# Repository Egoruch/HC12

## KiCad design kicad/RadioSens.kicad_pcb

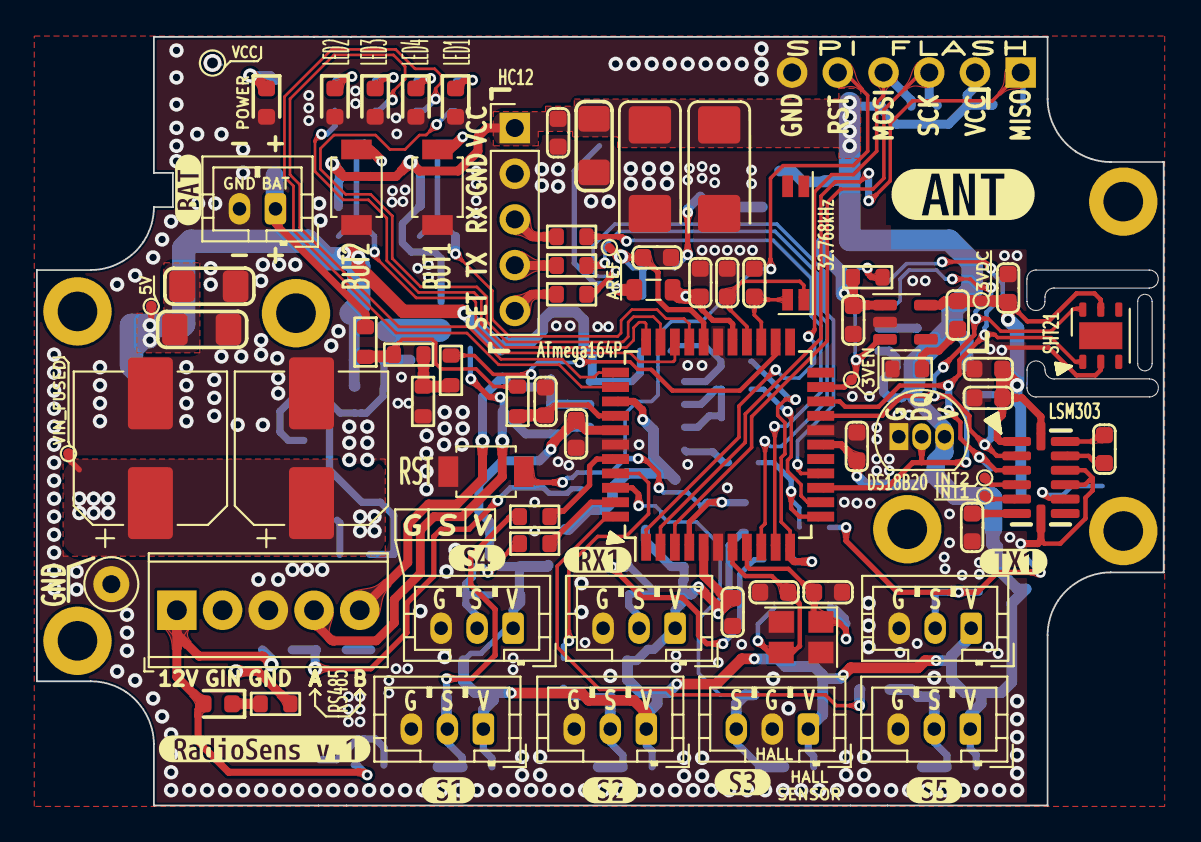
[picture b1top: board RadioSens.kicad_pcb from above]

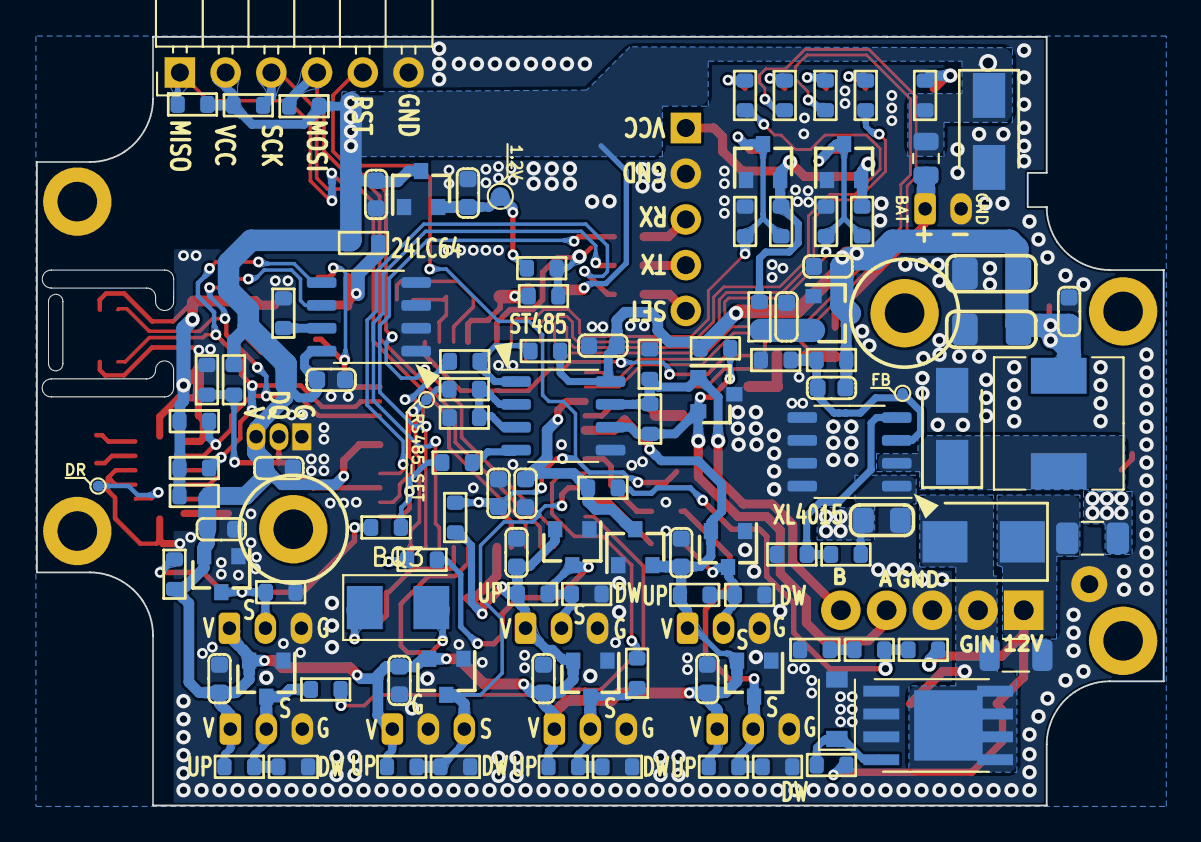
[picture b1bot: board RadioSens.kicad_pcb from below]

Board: 2 copper layers, 62.6 x 42.7 mm, 200 parts (110 on the bottom side), 81 nets.

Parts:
BQ1: KX–327L; Crystal_SMD_SeikoEpson_MC146-4Pin_6.7x1.5mm
BQ2: 3225 8MHz; Crystal_SMD_3225-4Pin_3.2x2.5mm
BQ3: 5032 8MHz; Crystal_SMD_5032-2Pin_5.0x3.2mm
C1, C7, C9, C30, C43, C45: 1u/25V; C_0603_1608Metric
C2, C6, C8, C10, C11, C12, C13, C15, C19, C22, C23, C24, C25, C36, C37, C40, C44: 0.1u/50V; C_0603_1608Metric
C3, C4: 100u/10V; CP_EIA-6032-28_Kemet-C
C5: 10u/16V; C_1206_3216Metric_Pad1.42x1.75mm_HandSolder
C14, C17: 7/50V; C_0603_1608Metric
C16, C18, C35, C41, C42: 10u/6.3V; C_0603_1608Metric
C20, C21: 22/50V; C_0603_1608Metric
C26, C27: 47u/50V; CP_Elec_8x6.5
C28: 1u/50V; C_0805_2012Metric_Pad1.15x1.40mm_HandSolder
C29: 3.3n/50V; C_0603_1608Metric
C31, C32, C33, C34: 100u/6.3V; C_1206_3216Metric_Pad1.42x1.75mm_HandSolder
C38: 4.7u/6.3V; C_0603_1608Metric
C39: 0.22u/50V; C_0603_1608Metric
C46: 2.2u/25V; C_0603_1608Metric
DA1: HC-12; HC12_PLS
DA2: XC6206P122MR-G; SOT-23
DA3: XL1509; SOP-8_3.9x4.9mm_P1.27mm
DA4: SHT21; DFN-6-1EP_3x3mm_P1mm_EP1.5x2.4mm
DA5: XC6206P332MR; SOT-23
DA6: LP2981-30DBVR; SOT-23-5
DD1: ATmega164PV-10AU; TQFP-44_10x10mm_P0.8mm
DD2: ST485; SOP-8_3.9x4.9mm_P1.27mm
DD3: DS18B20; TO-92_Inline
DD4: LSM303DLHC; LGA-14_3x5mm_P0.8mm_HandSoldering
DD5: 24LC64; SOP-8_3.9x4.9mm_P1.27mm
FU1: 0.3A; Fuse_0805_2012Metric
FU2: 1A; Fuse_1206_3216Metric
HL1, HL2, HL3, HL4, HL5, HL6: RED; LED_0603_1608Metric
J1, J2, J3, J4, J5, J6: Spacer M2; MountingHole_2.2mm_M2_DIN965_Pad
L1: 10u; L_0805_2012Metric
L2: 47uH/2A; L_Wuerth_HCM-7050
R1, R2, R3, R29, R30, R49, R50, R61, R66, R71: 0; R_0603_1608Metric
R4, R5, R6, R16, R17, R18: 22; R_0603_1608Metric
R7, R8, R9, R11, R68: 10k; R_0603_1608Metric
R10: 120; R_0603_1608Metric
R12, R19, R20, R21, R27, R47, R48, R51, R52, R53, R54, R59, R60, R62, R64, R69, R70: 4.7k; R_0603_1608Metric
R13, R14, R22, R23, R24, R25, R31, R33, R34, R36, R37, R38, R39, R41, R42, R44, R45, R67: 300k; R_0603_1608Metric
R15, R26, R28, R35, R40, R43, R46, R65: 100; R_0603_1608Metric
R32, R55, R56: 100k; R_0603_1608Metric
R57: 3.1k; R_0603_1608Metric
R58: 1k; R_0603_1608Metric
R63: 0; R_1206_3216Metric
R72: 1; R_0603_1608Metric
SB1, SB2, SB3: 3x4mm; SW_SPST_B3U-1000P
VD1: CDSOT23-SM712; SOT-23
VD2, VD3, VD4, VD6, VD7, VD8, VD9, VD10, VD14, VD15: BAT54S.215; SOT-23
VD5: SMAJ5.0A; D_SMA
VD11: MBRA340T3G; D_SMA
VD12: SMBJ28CA; D_SMB
VD13: BZT52-C9V1; D_SOD-123
VT1: SIR182DP; PowerPAK_SO-8_Single_HandSoldering
XB1, XB5, XB6, XB7, XB8, XB9, XB10, XB11, XB12: XB_TP_0.6MM; TestPoint_Pad_D0.6mm
XB2, XB3: XB_TP_1.0MM; TestPoint_Pad_D1.0mm
XB4: XB_TP_0.5MM; TestPoint_Pad_D0.5mm
XP9: Testpoint; TestPoint_Loop_D2.50mm_Drill1.0mm_LowProfile
XT1: DG308-2.54-05P-14-00A[H]; TerminalBlock_DG308-2.54-05P-14-00A(H)
XT2, XT3, XT5, XT6, XT7, XT8, XT10: NXW-03; JST_PH_B3B-PH-K_1x03_P2.00mm_Vertical
XT4: NXW-02; JST_PH_B2B-PH-K_1x02_P2.00mm_Vertical
XT9: PLS2.54-6; PinHeader_1x06_P2.54mm_Horizontal
kibuzzard-633978AE: G***; kibuzzard-633978AE
kibuzzard-633978C2: G***; kibuzzard-633978C2
kibuzzard-633978F6: G***; kibuzzard-633978F6
kibuzzard-633979A2: G***; kibuzzard-633979A2
kibuzzard-6339783C: G***; kibuzzard-6339783C
kibuzzard-6339785C: G***; kibuzzard-6339785C
kibuzzard-6339789C: G***; kibuzzard-6339789C
kibuzzard-63397779: G***; kibuzzard-63397779
kibuzzard-63397848: G***; kibuzzard-63397848
kibuzzard-63397852: G***; kibuzzard-63397852

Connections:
3V_EN: DA6.3 (ON/OFF), DD1.21 (PC2_PCINT18/TCK), R71.1, XB11.1
5V: C1.1, C29.1, C30.1, C31.1, C32.1, C33.1, C34.1, C41.1, DA5.3 (IN), DD2.8 (VCC), L2.2, R8.2, R9.2, R57.1, XB7.1
12V: FU2.1, HL6.2 (C), R62.1, R67.1, VD12.1 (C), XT1.1
/3VDC: C35.1, C36.1, C37.1, C46.2, DA4.5 (VDD), DA6.5 (VOUT), DD4.1 (VDDIO), DD4.14 (VDD), R3.2, R59.1, R60.1, XB12.1
/Battery/BAT_UNFUSED: FU1.2, R31.1, XT4.1
/DC-DC XL1509/EN: DA3.4 (EN), R55.2, R56.1
/DC-DC XL1509/FB: C29.2, DA3.3 (FB), R57.2, R58.1, XB6.1
/DC-DC XL1509/OUT: DA3.2 (OUT), L2.1, VD11.1 (C)
/DC-DC XL1509/VIN_FUSED: C26.1 (+), C27.1 (+), C28.1, DA3.1 (VIN), FU2.2, R55.1, XB5.1
/GND_RAW: R63.2, R64.1, VD12.2 (A), VT1.5 (D), VT1.6 (D), VT1.7 (D), VT1.8 (D), XT1.2
/IIC Connector/C1: C38.1, DD4.6 (C1)
/IIC Connector/INT1: DD4.5 (INT1), XB9.1
/IIC Connector/INT2: DD4.4 (INT2), XB8.1
/IIC Connector/SETC: C39.1, DD4.13 (SETC)
/IIC Connector/SETP: C39.2, DD4.12 (SETP)
/RS485/A_RS485: DD2.6 (A), R9.1, R10.2, VD1.2 (C2), XT1.4
/RS485/B_RS485: DD2.7 (B), R10.1, R11.2, VD1.1 (C1), XT1.5
/RS485/DE: DD2.2 (RE), DD2.3 (DE), R5.2, R7.2
/Sensor 1/SIGNAL: R13.2, R14.1, R15.2, VD2.3 (CA), XT2.2
/Sensor 2/SIGNAL: R38.2, R39.1, R40.2, VD8.3 (CA), XT6.2
/Sensor 4/SIGNAL: R41.2, R42.1, R43.2, VD9.3 (CA), XT7.2
/Sensor 5/SIGNAL: R44.2, R45.1, R46.2, VD10.3 (CA), XT8.2
/Sensor 6/SIGNAL: R24.2, R25.1, R26.2, VD4.3 (CA), XT3.2
/Sensor 7/SIGNAL: R33.2, R34.1, R35.2, VD6.3 (CA), XT5.2
/Voltage Regulator 3.3V/VOUT: C42.1, DA5.2 (OUT), R1.2
/Voltage Regulator 3V/VIN: C45.1, DA6.1 (VIN), R2.2, R71.2
ADC_BAT_VOL: C9.1, DD1.37 (PA0_ADC0/PCINT0), R28.1
ADC_EXTERN_VOL: C43.1, DD1.36 (PA1_ADC1/PCINT1), R65.1, VD14.3 (CA)
AREF: C19.2, DD1.29 (AREF), R49.2, R50.2, XB4.1
AVCC: C15.2, DD1.27 (AVCC), L1.2, R49.1
BAT_DIV_EN: DD1.24 (PC5_TDI/PCINT21), R29.1
BUT_1: DD1.30 (PA7_ADC7/PCINT7), R36.2, R37.1, SB2.1, VD7.3 (CA)
BUT_2: DD1.31 (PA6_ADC6/PCINT6), R22.2, R23.1, SB1.1, VD3.3 (CA)
DS18B20_DQ: DD1.14 (PD5_PCINT29/OC1A), DD3.2 (DQ), R19.2, R20.1
GND: BQ2.2 (GND), BQ2.4 (GND), C1.2, C2.2, C3.2 (-), C4.2 (-), C5.2, C6.2, C7.2, C8.2, C9.2, C10.2, C11.2, C12.2, C13.2, C14.2, C15.1, C16.2, C17.2, C18.2, C19.1, C20.2, C21.2, C22.2, C23.2, C24.1, C25.2, C26.2 (-), C27.2 (-), C28.2, C30.2, C31.2, C32.2, C33.2, C34.2, C35.2, C36.2, C37.2, C38.2, C40.2, C41.2, C42.2, C43.2, C44.2, C45.2, DA1.2 (GND), DA2.1 (GND), DA3.5 (GND), DA3.6 (GND), DA3.7 (GND), DA3.8 (GND), DA4.2 (VSS), DA5.1 (GND), DA6.2 (GND), DD1.6 (GND), DD1.18 (GND), DD1.28 (GND), DD1.39 (GND), DD2.5 (GND), DD3.1 (GND), DD4.7 (GND), DD4.10 (GND), DD4.11 (GND), DD5.1 (A0), DD5.2 (A1), DD5.3 (A2), DD5.4 (VSS), HL1.2 (C), HL2.2 (C), HL3.2 (C), HL4.2 (C), HL5.2 (C), R7.1, R11.1, R14.2, R20.2, R23.2, R25.2, R30.1, R34.2, R37.2, R39.2, R42.2, R45.2, R56.2, R58.2, R61.2, R63.1, R66.1, R70.2, R72.1, SB1.2, SB2.2, SB3.1, VD1.3 (DC), VD2.1 (A), VD3.1 (A), VD4.1 (A), VD5.2 (A), VD6.1 (A), VD7.1 (A), VD8.1 (A), VD9.1 (A), VD10.1 (A), VD11.2 (A), VD13.2 (A), VD14.1 (A), VD15.1 (A), VT1.1 (S), VT1.2 (S), VT1.3 (S), XP9.1, XT1.3, XT2.3, XT3.3, XT4.2, XT5.3, XT6.3, XT7.3, XT8.3, XT9.6, XT10.2
HC12_SET: DD1.15 (PD6_PCINT30/OC2B/ICP), R18.2
IIC_SCL: DA4.6 (SCL), DD1.19 (PC0_PCINT16/SCL), DD4.2 (SCL), DD5.6 (SCL), R60.2
IIC_SDA: DA4.1 (SDA), DD1.20 (PC1_PCINT17/SDA), DD4.3 (SDA), DD5.5 (SDA), R59.2
LED_1: DD1.32 (PA5_ADC5/PCINT5), R21.1
LED_2: DD1.33 (PA4_ADC4/PCINT4), R12.1
LED_3: DD1.34 (PA3_ADC3/PCINT3), R47.1
LED_4: DD1.35 (PA2_ADC2/PCINT2), R48.1
MISO: DD1.2 (PB6_PCINT14/OC3A/MISO), R53.2, XT9.1
MOSI: DD1.1 (PB5_PCINT13/ICP3/MOSI), R51.2, XT9.4
unnamed: C18.1, DA2.2 (OUT), R50.1, XB3.1
unnamed: C46.1, R72.2
unnamed: DA1.3 (RXD), R16.1
unnamed: DA1.4 (TXD), R17.1
unnamed: DA1.5 (SET), R18.1
unnamed: DD2.1 (RO), R4.2, R8.1
unnamed: DD2.4 (DI), R6.2
unnamed: DD4.9 (DRDY), XB10.1
unnamed: DD5.7 (WP), R61.1
unnamed: HL1.1 (A), R12.2
unnamed: HL2.1 (A), R21.2
unnamed: HL3.1 (A), R27.2
unnamed: HL4.1 (A), R47.2
unnamed: HL5.1 (A), R48.2
unnamed: HL6.1 (A), R64.2
unnamed: R28.2, R31.2, R32.1
unnamed: R29.2, R30.2, R32.2
unnamed: R62.2, VD13.1 (C), VT1.4 (G)
unnamed: R65.2, R67.2, R68.1
unnamed: R66.2, R68.2
RESET: C25.1, DD1.4 (~RESET), R54.2, SB3.2, XT9.5
RS485_SET: DD1.13 (PD4_PCINT28/XCK1/OC1B), R5.1, XB1.1
RXD0: DD1.9 (PD0_PCINT24/RXD0/T3*), R17.2
RXD1: DD1.11 (PD2_PCINT26/RXD1/INT0), R4.1, R26.1
SCK: DD1.3 (PB7_PCINT15/OC3B/SCK), R52.2, XT9.3
SENS_1: DD1.40 (PB0_XCK0/T0/PCINT8), R15.1
SENS_2: DD1.41 (PB1_T1/CLKO/PCINT9), R40.1
SENS_3: DD1.42 (PB2_AIN0/INT2/PCINT10), R69.2, R70.1, VD15.3 (CA), XT10.3
SENS_4: DD1.43 (PB3_AIN1/OC0A/PCINT11), R43.1
SENS_5: DD1.44 (PB4_SS/OC0B/PCINT12), R46.1
TOSC1: BQ1.4, C14.1, DD1.25 (PC6_TOSC1/PCINT22)
TOSC2: BQ1.1, C17.1, DD1.26 (PC7_TOSC2/PCINT23)
TXD0: DD1.10 (PD1_PCINT25/TXD0), R16.2
TXD1: DD1.12 (PD3_PCINT27/TXD1/INT1), R6.1, R35.1
VCC: C2.1, C3.1 (+), C4.1 (+), C5.1, C6.1, C7.1, C8.1, C10.1, C11.1, C12.1, C13.1, C16.1, C22.1, C23.1, C24.2, C40.1, C44.1, DA1.1 (VCC), DA2.3 (IN), DD1.5 (VCC), DD1.17 (VCC), DD1.38 (VCC), DD3.3 (VDD), DD5.8 (VCC), FU1.1, L1.1, R1.1, R2.1, R3.1, R13.1, R19.1, R22.1, R24.1, R27.1, R33.1, R36.1, R38.1, R41.1, R44.1, R51.1, R52.1, R53.1, R54.1, R69.1, VD2.2 (C), VD3.2 (C), VD4.2 (C), VD5.1 (C), VD6.2 (C), VD7.2 (C), VD8.2 (C), VD9.2 (C), VD10.2 (C), VD14.2 (C), VD15.2 (C), XB2.1, XT2.1, XT3.1, XT5.1, XT6.1, XT7.1, XT8.1, XT9.2, XT10.1
XTAL1: BQ2.1 (IN), BQ3.1, C20.1, DD1.8 (XTAL1)
XTAL2: BQ2.3 (OUT), BQ3.2, C21.1, DD1.7 (XTAL2)

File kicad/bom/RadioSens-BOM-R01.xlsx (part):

Project: | RadioSens v.1 | COMPANY NAME
Author:
Date: | 44722.0
Item | Qty | Reference(s) | Value | Footprint/Package | Tolerance | Type | Comment | Cost, UAH | Total cost, UAH | Buy | Link
1.0 | 1.0 | BQ1 | KX–327L | Crystal:Crystal_SMD_SeikoEpson_MC146-4Pin_6.7x1.5mm |  |  |  | 10.0 | 10 | 0 | https://www.rcscomponents.kiev.ua/product/kx-327lt-32-7680-k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
2.0 | 1.0 | BQ2 | 3225 8MHz | Crystal:Crystal_SMD_3225-4Pin_3.2x2.5mm |  |  | 4MHz optional | 21.5 | 21.5 | 0 | https://voron.ua/uk/catalog/037612
3.0 | 1.0 | BQ3 | 5032 8MHz | Crystal:Crystal_SMD_5032-2Pin_5.0x3.2mm |  |  | Extra package | 0.0 | 0 | 1 | DNP
4.0 | 5.0 | C1, C7, C9, C43, C45 | 1u/25V | Capacitor_SMD:C_0603_1608Metric | ±10% | X5R/X7R |  | 0.9 | 4.5 | 0 | https://www.rcscomponents.kiev.ua/product/1uf-25v-x7r-10-060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
5.0 | 8.0 | C2, C6, C8, C10, C11, C12, C13, C44 | 0.1u/50V | Capacitor_SMD:C_0603_1608Metric | ±10% | X5R/X7R |  | 0.9 | 7.2 | 0 | https://www.rcscomponents.kiev.ua/product/100nf-50v-x7r-10-0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
6.0 | 2.0 | C3, C4 | 100u/10V | Capacitor_Tantalum_SMD:CP_EIA-6032-28_Kemet-C |  |  | Alt: Type-B | 0.9 | 1.8 | 0 | https://www.rcscomponents.kiev.ua/product/100uf-6-3v-size-b-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
7.0 | 1.0 | C5 | 10u/16V | Capacitor_SMD:C_1206_3216Metric_Pad1.42x1.75mm_HandSolder | ±10% | X5R/X7R | Alt: 47u/50V | 4.0 | 4 | 0 | https://www.rcscomponents.kiev.ua/product/47uf-50v-ezv-smd-s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
8.0 | 1.0 | C14 | 7/50V | Capacitor_SMD:C_0603_1608Metric | ±10% | X5R/X7R | Alt: 6.8pF | 0.5 | 0.5 | 0 | https://www.rcscomponents.kiev.ua/product/6-8pf-50v-np0-0-5p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
9.0 | 2.0 | C15, C40 | 0.1u/50V | Capacitor_SMD:C_0603_1608Metric | ±10% | X5R/X7R |  | 0.9 | 1.8 | 0 | https://www.rcscomponents.kiev.ua/product/100nf-50v-x7r-10-0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
10.0 | 2.0 | C16, C35 | 10u/6.3V | Capacitor_SMD:C_0603_1608Metric | ±10% | X5R/X7R |  | 1.0 | 2 | 0 | https://www.rcscomponents.kiev.ua/product/10uf-6-3v-x5r-20-0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
11.0 | 1.0 | C17 | 7/50V | Capacitor_SMD:C_0603_1608Metric | ±10% | X5R/X7R | Alt: 6.8pF | 0.5 | 0.5 | 0 | https://www.rcscomponents.kiev.ua/product/6-8pf-50v-np0-0-5p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
12.0 | 1.0 | C18 | 10u/6.3V | Capacitor_SMD:C_0603_1608Metric | ±10% | X5R/X7R |  | 1.0 | 1 | 0 | https://www.rcscomponents.kiev.ua/product/10uf-6-3v-x5r-20-0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
13.0 | 1.0 | C19 | 0.1u/50V | Capacitor_SMD:C_0603_1608Metric | ±10% | X5R/X7R |  | 0.9 | 0.9 | 0 | https://www.rcscomponents.kiev.ua/product/100nf-50v-x7r-10-0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
14.0 | 1.0 | C20 | 22/50V | Capacitor_SMD:C_0603_1608Metric | ±10% | X5R/X7R |  | 0.4 | 0.4 | 0 | https://www.rcscomponents.kiev.ua/product/22pf-50v-np0-5-060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
15.0 | 1.0 | C21 | 22/50V | Capacitor_SMD:C_0603_1608Metric | ±10% | X5R/X7R |  | 0.4 | 0.4 | 0 | https://www.rcscomponents.kiev.ua/product/22pf-50v-np0-5-060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
16.0 | 1.0 | C22 | 0.1u/50V | Capacitor_SMD:C_0603_1608Metric | ±10% | X5R/X7R |  | 0.9 | 0.9 | 0 | https://www.rcscomponents.kiev.ua/product/100nf-50v-x7r-10-0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
17.0 | 1.0 | C23 | 0.1u/50V | Capacitor_SMD:C_0603_1608Metric | ±10% | X5R/X7R |  | 0.9 | 0.9 | 0 | https://www.rcscomponents.kiev.ua/product/100nf-50v-x7r-10-0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
18.0 | 1.0 | C24 | 0.1u/50V | Capacitor_SMD:C_0603_1608Metric | ±10% | X5R/X7R |  | 0.9 | 0.9 | 0 | https://www.rcscomponents.kiev.ua/product/100nf-50v-x7r-10-0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
19.0 | 1.0 | C25 | 0.1u/50V | Capacitor_SMD:C_0603_1608Metric | ±10% | X5R/X7R |  | 0.9 | 0.9 | 0 | https://www.rcscomponents.kiev.ua/product/100nf-50v-x7r-10-0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
20.0 | 2.0 | C26, C27 | 22u/50V | Capacitor_SMD:CP_Elec_8x6.5 |  |  | Alt: 47u/50V | 4.0 | 8 | 0 | https://www.rcscomponents.kiev.ua/product/47uf-50v-ezv-smd-s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
21.0 | 1.0 | C28 | 1u/50V | Capacitor_SMD:C_0805_2012Metric_Pad1.15x1.40mm_HandSolder | ±10% | X5R/X7R |  | 1.6 | 1.6 | 0 | https://www.rcscomponents.kiev.ua/product/1uf-50v-x7r-10-080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
22.0 | 1.0 | C29 | 3.3n/50V | Capacitor_SMD:C_0603_1608Metric | ±10% | X5R/X7R |  | 0.5 | 0.5 | 0 | https://www.rcscomponents.kiev.ua/product/3-3nf-50v-x7r-10-0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
23.0 | 1.0 | C30 | 1u/25V | Capacitor_SMD:C_0603_1608Metric | ±10% | X5R/X7R |  | 0.9 | 0.9 | 0 | https://www.rcscomponents.kiev.ua/product/1uf-25v-x7r-10-060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
24.0 | 1.0 | C31 | 100u/6.3V | Capacitor_SMD:C_1206_3216Metric_Pad1.42x1.75mm_HandSolder | ±10% | X5R/X7R | Alt: 47u/6.3V | 3.5 | 3.5 | 0 | https://www.rcscomponents.kiev.ua/product/47uf-6-3v-x5r-20-1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
25.0 | 1.0 | C32 | 100u/6.3V | Capacitor_SMD:C_1206_3216Metric_Pad1.42x1.75mm_HandSolder | ±10% | X5R/X7R | Alt: 47u/6.3V | 3.5 | 3.5 | 0 | https://www.rcscomponents.kiev.ua/product/47uf-6-3v-x5r-20-1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
26.0 | 1.0 | C33 | 100u/6.3V | Capacitor_SMD:C_1206_3216Metric_Pad1.42x1.75mm_HandSolder | ±10% | X5R/X7R | Alt: 47u/6.3V | 3.5 | 3.5 | 0 | https://www.rcscomponents.kiev.ua/product/47uf-6-3v-x5r-20-1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
27.0 | 1.0 | C34 | 100u/6.3V | Capacitor_SMD:C_1206_3216Metric_Pad1.42x1.75mm_HandSolder | ±10% | X5R/X7R | Alt: 47u/6.3V | 3.5 | 3.5 | 0 | https://www.rcscomponents.kiev.ua/product/47uf-6-3v-x5r-20-1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
28.0 | 1.0 | C36 | 0.1u/50V | Capacitor_SMD:C_0603_1608Metric | ±10% | X5R/X7R |  | 0.9 | 0.9 | 0 | https://www.rcscomponents.kiev.ua/product/100nf-50v-x7r-10-0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
29.0 | 1.0 | C37 | 0.1u/50V | Capacitor_SMD:C_0603_1608Metric | ±10% | X5R/X7R |  | 0.9 | 0.9 | 0 | https://www.rcscomponents.kiev.ua/product/100nf-50v-x7r-10-0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
30.0 | 1.0 | C38 | 4.7u/25V | Capacitor_SMD:C_0603_1608Metric | ±10% | X5R/X7R |  | 1.3 | 1.3 | 0 | https://www.rcscomponents.kiev.ua/product/4-7uf-6-3v-x5r-10-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
31.0 | 1.0 | C39 | 0.22u/50V | Capacitor_SMD:C_0603_1608Metric | ±10% | X5R/X7R |  | 0.5 | 0.5 | 0 | https://www.rcscomponents.kiev.ua/product/220nf-16v-x7r-10-0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
32.0 | 1.0 | C41 | 10u/6.3V | Capacitor_SMD:C_0603_1608Metric | ±10% | X5R/X7R |  | 1.0 | 1 | 0 | https://www.rcscomponents.kiev.ua/product/10uf-6-3v-x5r-20-0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
33.0 | 1.0 | C42 | 10u/6.3V | Capacitor_SMD:C_0603_1608Metric | ±10% | X5R/X7R |  | 1.0 | 1 | 0 | https://www.rcscomponents.kiev.ua/product/10uf-6-3v-x5r-20-0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
34.0 | 1.0 | C46 | 2.2u/25V | Capacitor_SMD:C_0603_1608Metric | ±10% | X5R/X7R |  | 1.4 | 1.4 | 0 | https://www.rcscomponents.kiev.ua/product/2-2uf-50v-x5r-10-0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
35.0 | 1.0 | DA1 | HC-12 | RF_Module:HC12_PLS |  |  |  | 199.8 | 199.8 | 0 | https://imrad.com.ua/ru/bluetooth-modul-hc-12-na-si4463
36.0 | 1.0 | DA2 | XC6206P122MR-G | Package_TO_SOT_SMD:SOT-23 |  |  |  |  | 0 | 0
37.0 | 1.0 | DA3 | XL1509 | Package_SO:SOP-8_3.9x4.9mm_P1.27mm |  |  |  | 15.5 | 15.5 | 0 | http://www.kosmodrom.com.ua/el.php?name=XL1509-ADJE1
38.0 | 1.0 | DA4 | SHT21 | Package_DFN_QFN:DFN-6-1EP_3x3mm_P1mm_EP1.5x2.4mm |  |  | 1 PCS | 344.0 | 344 | 0 | http://www.kosmodrom.com.ua/el.php?name=SHT21-MODUL
39.0 | 1.0 | DA5 | XC6206P332MR | Package_TO_SOT_SMD:SOT-23 |  |  |  | 10.5 | 10.5 | 0 | http://www.kosmodrom.com.ua/el.php?name=XC6206P332MR
40.0 | 1.0 | DA6 | LP2981-30DBVR | Package_TO_SOT_SMD:SOT-23-5 |  |  |  | 15.5 | 15.5 | 0 | https://www.rcscomponents.kiev.ua/product/lp2981-30dbvr_30511.html
41.0 | 1.0 | DD1 | ATmega164PV-10AU | Package_QFP:TQFP-44_10x10mm_P0.8mm |  |  | Alt: ATmega164PA-AU | 306.0 | 306 | 0 | http://www.kosmodrom.com.ua/el.php?name=ATmega164PA-AU
42.0 | 1.0 | DD2 | ST485 | Package_SO:SOP-8_3.9x4.9mm_P1.27mm |  |  |  | 29.5 | 29.5 | 0 | http://www.kosmodrom.com.ua/el.php?name=ST485BDR
43.0 | 1.0 | DD3 | DS18B20 | Package_TO_SOT_THT:TO-92_Inline |  |  |  | 78.12 | 78.12 | 0 | https://imrad.com.ua/ua/ds18b20-
44.0 | 1.0 | DD4 | LSM303DLHC | Package_LGA:LGA-14_3x5mm_P0.8mm_HandSoldering |  |  |  | 120.06 | 120.06 | 0 | https://imrad.com.ua/ua/lsm303dlhc-0
45.0 | 1.0 | DD5 | 24LC64 | Package_SO:SOP-8_3.9x4.9mm_P1.27mm |  |  |  | 11.53 | 11.53 | 0 | https://imrad.com.ua/ua/24lc64-i-sn
46.0 | 1.0 | FU1 | 0.3A | Fuse:Fuse_0805_2012Metric |  |  | Alt: 0.2A | 3.01 | 3.01 | 0 | https://voron.ua/uk/catalog/029387--predohranitel_ptc_smd_08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
47.0 | 1.0 | FU2 | 1A | Fuse:Fuse_1206_3216Metric |  |  |  |  | 0 | 0
48.0 | 2.0 | GB1, GB2 | ER14505 |  |  |  | Battery | 155.0 | 310 | 1 | https://www.rcscomponents.kiev.ua/product/ls14500-pfr-saft-l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
49.0 | 6.0 | HL1, HL2, HL3, HL4, HL5, HL6 | RED | LED_SMD:LED_0603_1608Metric |  |  |  | 0.301 | 1.806 | 0 | https://voron.ua/uk/catalog/038156
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
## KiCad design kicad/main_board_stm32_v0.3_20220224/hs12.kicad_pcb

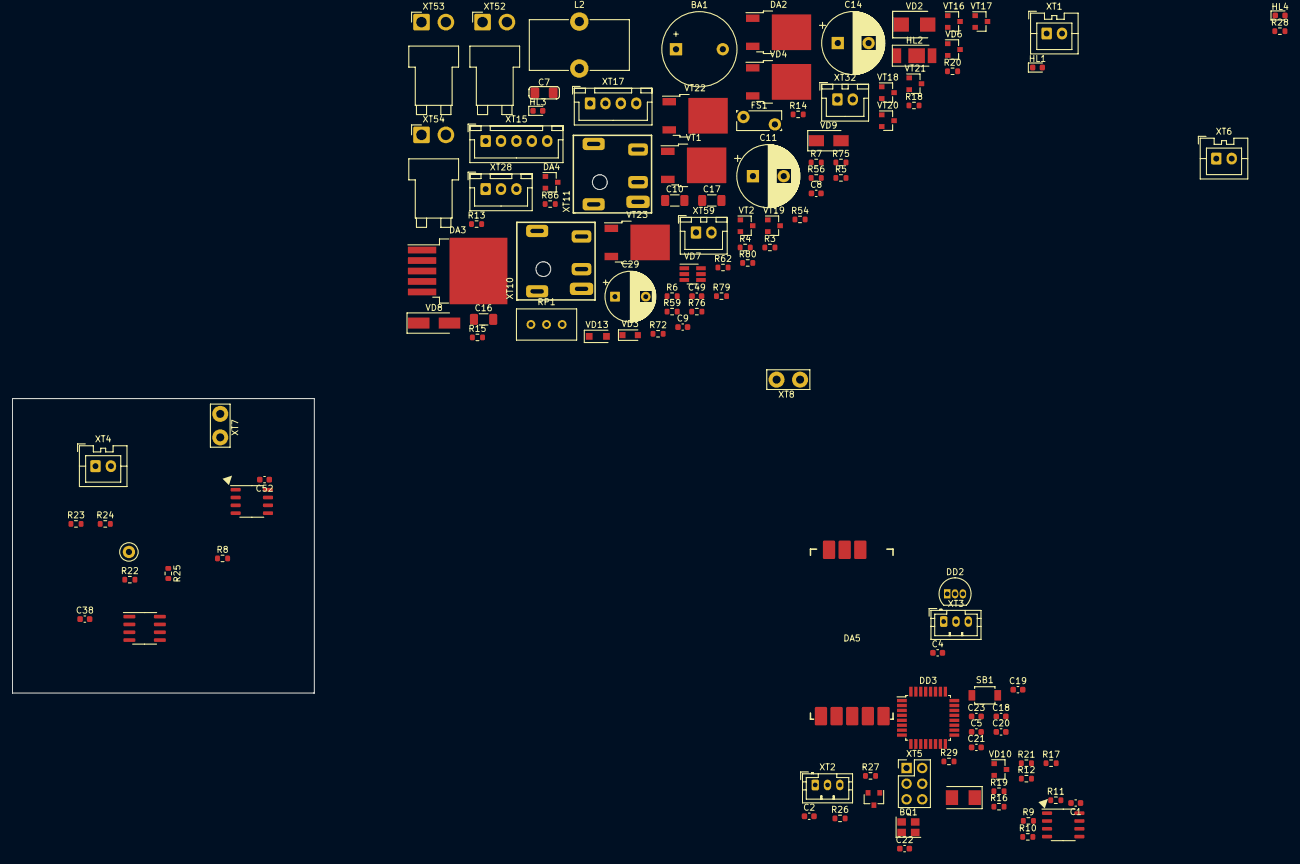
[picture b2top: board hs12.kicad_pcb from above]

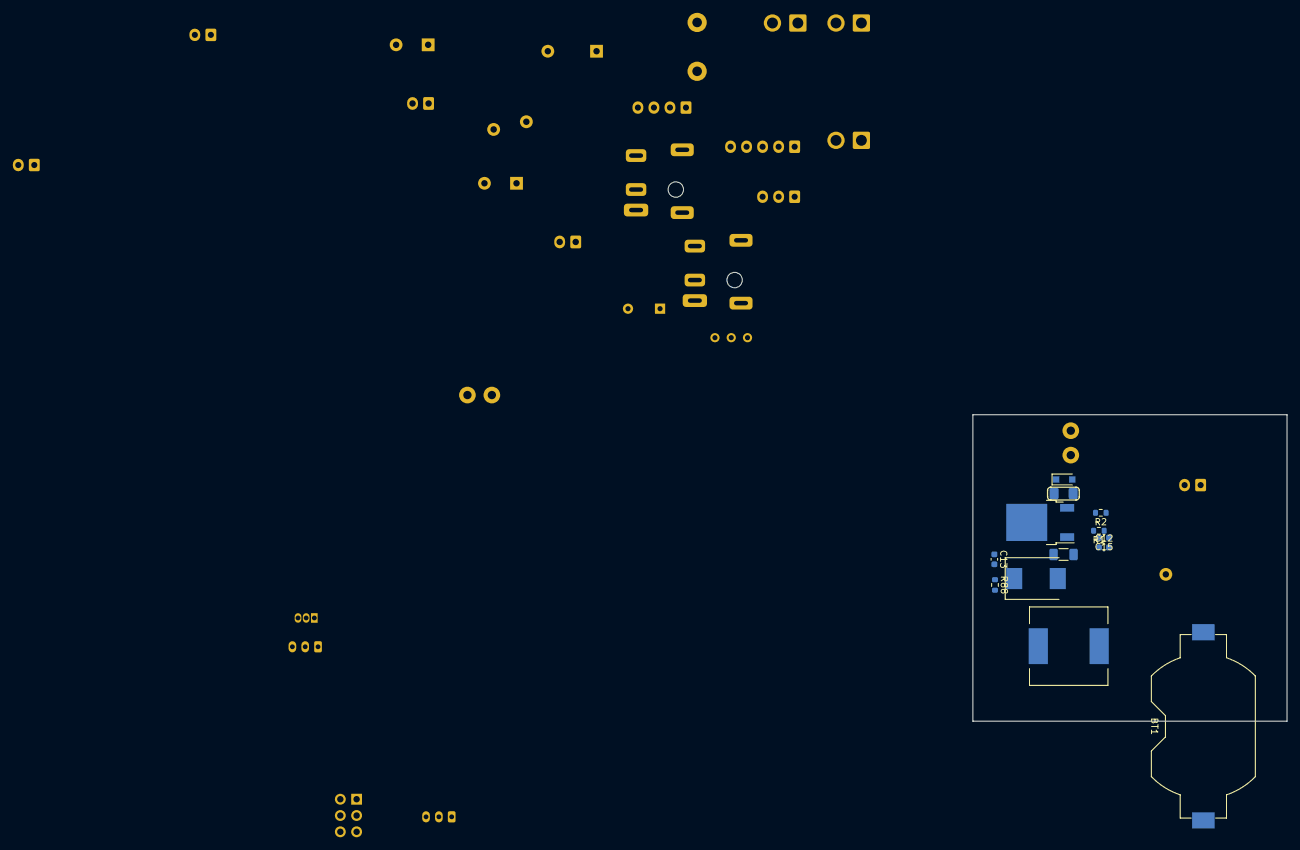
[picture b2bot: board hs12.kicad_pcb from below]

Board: 2 copper layers, 49.0 x 47.8 mm, 131 parts (13 on the bottom side), 66 nets, no tracks yet.

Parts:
BA1: BUZZER 12x9.5mm; Buzzer_12x9.5RM7.6
BQ1: 3225 25MHz; Crystal_SMD_3225-4Pin_3.2x2.5mm
BQ2: 5032 25MHz; Crystal_SMD_5032-2Pin_5.0x3.2mm
BT1: Battery_Cell; BatteryHolder_Keystone_1058_1x2032
C1, C12, C13, C38: 1u; C_0603_1608Metric
C2, C4, C8, C9, C18, C20, C21, C22, C23, C49, C52: 0.1u; C_0603_1608Metric
C3, C7: 10u; C_1206_3216Metric_Pad1.42x1.75mm_HandSolder
C5, C19: 22; C_0603_1608Metric
C6, C10, C16, C17: 10u; C_1206_3216Metric_Pad1.33x1.80mm_HandSolder
C11: 220u/50V; CP_Radial_D10.0mm_P5.00mm
C14: 330u/25V; CP_Radial_D10.0mm_P5.00mm
C15: 33n; C_0603_1608Metric
C29: 220u/25V; CP_Radial_D8.0mm_P5.00mm
DA1: AMS1117CD-3.3; TO-252-2
DA2: L78M05CDT-TR; TO-252-2
DA3: XL4005; TO-263-5_TabPin6
DA4: XC6206P332MR; SOT-23
DA5: HC-12; HC12
DA9: 24LC64; SOP-8_3.9x4.9mm_P1.27mm
DD1: ST485; SOP-8_3.9x4.9mm_P1.27mm
DD2: DS18B20; TO-92_Inline
DD3: ATmega168P; TQFP-32_7x7mm_P0.8mm
FS1: 30R400UF 8A; Fuse_Bourns_MF-RG300
HL1, HL3, HL4: RED; LED_0603_1608Metric
HL2: WHITE5730; LED_5730
L1: 33uH/5A; L_Pulse_PA4320
L2: 33uH/5A; L_Toroid_Vertical_L16.0mm_W8.0mm_P7.62mm
R1, R16, R26, R27, R88: 10k; R_0603_1608Metric
R2, R7, R54: 1k; R_0603_1608Metric
R3, R5, R8, R62, R72, R79, R80: 0; R_0603_1608Metric
R4, R13, R20, R22, R56, R75: 10; R_0603_1608Metric
R6, R14, R15, R17, R18, R21, R23, R24, R25, R28, R29, R59, R76, R86: 4.7k; R_0603_1608Metric
R9, R10, R11, R12: 22; R_0603_1608Metric
R19: 120; R_0603_1608Metric
RP1: RP_TRIMMER; Potentiometer_Bourns_3296W_Vertical
SB1: SB_ON; SW_SPST_B3U-1000P
U21: DS1307ZN+; SOIC-8_3.9x4.9mm_P1.27mm
VD1, VD3: CDSOD323-T05SC; D_SOD-323_HandSoldering
VD2: SM6T12A; D_SMB
VD4: STPS8L30B; TO-252-2
VD5: MBRD1045G; D_SMC
VD6, VD10: VD_TVS_ARRAY4; SOT-23
VD7: SRV05-4.TCT; SOT-23-6_Handsoldering
VD8: 1N4007; D_SMA_Handsoldering
VD9: SS35; D_SMA
VD11: BAT54S.215; SOT-23
VD13: 1N4007; D_SOD-123F
VT1: IRFxxx; TO-252-2
VT2, VT18, VT19, VT21: IRLML2502; SOT-23
VT16: AO3407; SOT-23
VT17, VT20: BC847; SOT-23
VT22, VT23: XXXTO252; TO-252-2
XP1: Testpoint; TestPoint_Loop_D2.50mm_Drill1.0mm_LowProfile
XT1, XT4, XT6: XH2.54-2; JST_XA_B02B-XASK-1_1x02_P2.50mm_Vertical
XT2, XT3: XH2.54-3; JST_PH_B3B-PH-K_1x03_P2.00mm_Vertical
XT5: PLS-2x03; PinHeader_2x03_P2.54mm_Vertical
XT7, XT8: Jumper; TestPoint_Bridge_Pitch3.81mm_Drill1.3mm
XT10, XT11: DC044A 5.5/3.5mm; BarrelJack_DC044A_5.5_2.5mm_Horizontal
XT15: XH2.54-5; JST_XH_B5B-XH-A_1x05_P2.50mm_Vertical
XT17: XH2.54-4; JST_XH_B4B-XH-A_1x04_P2.50mm_Vertical
XT28: XH2.54-3; JST_XH_B3B-XH-A_1x03_P2.50mm_Vertical
XT32, XT59: XH2.54-2; JST_XH_B2B-XH-A_1x02_P2.50mm_Vertical
XT52, XT53, XT54: PWL-2R; JST_VH_B2PS-VH_1x02_P3.96mm_Horizontal

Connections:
3.3V: C6.1, C17.1, C49.1, C52.1, DA1.2 (GND), DA4.2 (OUT), DA9.8 (VCC), R14.1, R15.1, R80.1, R86.2, VD1.2 (C), VD7.5 (VP), XT15.2, XT17.3, XT28.3
5V: C3.1, C9.1, C10.1, C16.1, DA1.3 (OUTPUT), DA2.3 (OUTPUT), DA4.3 (IN), R79.1, VD3.2 (C), XP1.1, XT15.1
12V: C7.1, C8.1, DA2.1 (IN), R54.1, VD8.1 (K), VT16.2 (S), VT17.3 (C), XT32.2, XT52.1, XT53.1, XT54.1
12V_RAW: C13.1, C14.1, C15.1, C29.1, L1.2, L2.2, R1.2, R7.1, R88.2, VD2.2 (C), XT10.1, XT11.1
24V: C11.1, C12.1, DA3.4 (EN), DA3.5 (VIN)
/Battery/BAT+: BT1.1 (+), XT6.1
/Battery/BAT-: BT1.2 (-), XT6.2
/DS18B20/DQ: DD2.2 (DQ), XT3.1
/DS18B20/GND: C4.2, DD2.1 (GND), XT3.3
/DS18B20/VDD: C4.1, DD2.3 (VDD), XT3.2
/LED1/ANODE: R25.1, XT1.1
/LED1/CATHODE: HL1.2 (C), XT1.2
/LED/ANODE: R28.1, XT4.1
/LED/CATHODE: HL4.2 (C), XT4.2
/RS485/A_RS485: DD1.6 (A), R17.1, R19.2, VD10.2 (C2)
/RS485/B_RS485: DD1.7 (B), R19.1, R21.2, VD10.1 (C1)
/RS485/RS485_CTR: R10.1, R11.1
/Sensor/GND: C2.2, R27.2, VD11.1 (A), XT2.3
/Sensor/OUT: R26.2, R27.1, VD11.3 (CA), XT2.1
/Sensor/VCC: C2.1, R26.1, VD11.2 (C), XT2.2
BAT_VOL: C38.1, R22.1
D11_MOSI: DD3.15 (PB3_PCINT3/OC2A/MOSI), XT5.4
D12_MISO: DD3.16 (PB4_PCINT4/MISO), XT5.1
D13_SCK: DD3.17 (PB5_SCK/PCINT5), XT5.3
FB: C15.2, DA3.2 (FB), R1.1, R2.2, RP1.2
GND: BQ1.2 (GND), BQ1.4 (GND), C1.2, C3.2, C5.2, C6.2, C7.2, C8.2, C9.2, C10.2, C16.2, C17.2, C18.2, C19.2, C20.2, C21.2, C22.2, C23.1, C38.2, C49.2, C52.2, DA1.1 (IN), DA2.2 (GND), DA4.1 (GND), DA9.4 (VSS), DA9.7 (WP), DD1.5 (GND), DD3.3 (GND), DD3.5 (GND), DD3.21 (GND), HL3.2 (C), R3.2, R5.2, R6.2, R8.2, R21.1, R59.2, R76.2, SB1.1, VD1.1 (A), VD3.1 (A), VD6.3 (DC), VD7.2 (VN), VD10.3 (DC), VT1.3 (S), VT2.2 (S), VT18.2 (S), VT19.2 (S), VT20.2 (E), VT21.2 (S), VT22.3 (S), VT23.3 (S), XT5.6, XT7.1, XT8.1, XT15.5, XT17.4, XT28.2
GND_RAW: C13.2, C14.2, DA3.6 (BGND), FS1.2, R2.1, RP1.1, VD4.1 (NC), VD4.3 (A), VD5.1 (A), XT10.2, XT11.2
I2C_SCL: DA9.6 (SCL), R15.2, XT17.1
I2C_SDA: DA9.5 (SDA), R14.2, XT17.2
LED_PWM_5V: R72.2, R75.1, VT22.1 (G)
unnamed: BA1.1, R79.2, R80.2, VD13.1 (K), XT59.1
unnamed: BA1.2, HL2.2 (C), VD13.2 (A), VT2.3 (D), XT59.2
unnamed: C11.2, C12.2, DA3.1 (GND)
unnamed: C18.1, DD3.20 (AREF)
unnamed: C29.2, FS1.1, VD2.1 (A), VT1.2 (D)
unnamed: DA3.3 (SW), L1.1, L2.1, VD4.2 (C), VD5.2 (C)
unnamed: DA9.1 (A0), R3.1
unnamed: DA9.2 (A1), R5.1
unnamed: DA9.3 (A2), R8.1
unnamed: DD1.1 (RO), R9.2, R16.1
unnamed: DD1.2 (RE), DD1.3 (DE), R10.2, R11.2
unnamed: DD1.4 (DI), R12.2
unnamed: HL1.1 (A), R25.2
unnamed: HL2.1 (A), R86.1
unnamed: HL3.1 (A), R18.2
unnamed: HL4.1 (A), R28.2
unnamed: R4.1, R6.1, VT2.1 (G)
unnamed: R7.2, VT1.1 (G)
unnamed: R13.1, XT15.3
unnamed: R20.1, XT15.4
unnamed: R22.2, R23.2, R24.1
unnamed: R54.2, VT17.1 (B)
unnamed: R56.2, R59.1, R62.1, VT20.1 (B)
unnamed: R62.2, VT16.3 (D), VT18.3 (D), VT19.1 (G), VT23.1 (G)
unnamed: R75.2, R76.1, VT21.1 (G)
unnamed: R88.1, RP1.3
unnamed: VD8.2 (A), VT19.3 (D), VT23.2 (D), XT32.1
unnamed: VD9.1 (A), VT16.1 (G), VT17.2 (E), VT18.1 (G)
unnamed: VD9.2 (C), VT20.3 (C)
unnamed: VT21.3 (D), VT22.2 (D), XT52.2, XT53.2, XT54.2
RESET: C20.1, DD3.29 (PC6_RESET/PCINT14), R29.2, SB1.2, XT5.5
USART2_RX: R20.2, VD6.1 (C1)
USART2_TX: R13.2, VD6.2 (C2)
VCC: C1.1, C21.1, C22.1, C23.2, DD1.8 (VCC), DD3.4 (VCC), DD3.6 (VCC), DD3.18 (AVCC), R16.2, R17.2, R18.1, R29.1, XT5.2
XTAL1: BQ1.1 (IN), BQ2.1, C5.1, DD3.7 (PB6_PCINT6/XTAL1/TOSC1)
XTAL2: BQ1.3 (OUT), BQ2.2, C19.1, DD3.8 (PB7_PCINT7/XTAL2/TOSC2)

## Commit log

2022-10-04 Upload latest version; Rouring done, gerber out done
2022-10-04 Remove backups
2022-10-04 Reannotate schematic; Fix 5032 crystal footprint field; Update PCB with 5032 crystal
2022-10-06 Add voltage value to caps, update BOM, SCH, ASM
2022-10-06 Generate Gerber files with Paste layers
2022-10-06 Update work hours and last report
2022-10-28 Add docs; Update values of components according to PCB
2022-10-30 Add Vin.MIN=5.5V to schematic DC-DC note
2022-11-27 Add wiring diagram; Add work ours (stage 2); refactor folders
2023-05-08 add: more latest files
2023-09-27 update: readme
2023-09-27 init: issues list
2023-09-27 update: no changes
2023-09-27 remove: temporary kicad file
2023-09-27 change: grid origin
2023-09-27 update: to 7.0 ver and add fiducials
2023-09-27 add: another one fiducial
2023-10-04 update: gerber and add bom notes
2023-11-16 add: bom notes and asm files
2023-11-19 add: separated BOMs and modified common
